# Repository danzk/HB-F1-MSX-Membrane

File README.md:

# MSX Hit Bit Keyboard Membranes

Replacement keyboard membranes for Sony MSX "Hit Bit" home computers.

This repository hosts one design per machine, each in its own directory, all
sharing a common KiCad footprint library.

## Variants

| Machine | Directory | Notes |
| --- | --- | --- |
| Sony HB-F1 | [hb-f1/](hb-f1/) | Original design |
| Sony HB-F1II | [hb-f1ii/](hb-f1ii/) | Reworked PCB with revised switch footprint |

Each variant directory contains its own `pcb/` (KiCad project), `gerber/`
(fabrication outputs) and `mech/` (mechanical drawings), plus a `doc/`
folder for any variant-specific images. Reference material and renders
shared across variants live in the top-level [doc/](doc/) directory.

## Shared footprint library

Both projects reference the same footprints in
[footprints/Sony_Hit_Bit.pretty/](footprints/Sony_Hit_Bit.pretty/) via each
project's `fp-lib-table` (`${KIPRJMOD}/../../footprints/Sony_Hit_Bit.pretty`).

## Manufacturing

See [doc/MANUFACTURING.md](doc/MANUFACTURING.md) for how to order the membrane
from JLCPCB as a 2-layer flexible PCB (stackup, order settings and stiffener
details).

## Other projects

Related keyboard membrane / replacement projects for other Sony MSX models:

- [RBSC/KeyboardMembrane_SonyF1Xx](https://github.com/RBSC/KeyboardMembrane_SonyF1Xx)
  — replacement membrane PCB and gerbers for the Sony HB-F1XV, HB-F1XD and
  HB-F1XDJ.
- [S0urceror/HB-F1XD-keyboard](https://github.com/S0urceror/HB-F1XD-keyboard)
  — KiCad PCB replacement for the Sony HB-F1XD MSX2 keyboard membrane.

## Tooling

2D mechanical drawings were performed with QCAD v3.31.2.7 — https://www.qcad.org/

Electronics were designed with KiCad v8.0.7 — https://www.kicad.org/

The PCB layout uses the font IBM Plex Sans — https://www.ibm.com/plex/

## Licence

Copyright Alexander Knapik 2025.

This source describes Open Hardware and is licensed under the CERN-OHL-W v2 or later.

You may redistribute and modify this documentation and make products
using it under the terms of the CERN-OHL-W v2 (https://cern.ch/cern-ohl).
This documentation is distributed WITHOUT ANY EXPRESS OR IMPLIED
WARRANTY, INCLUDING OF MERCHANTABILITY, SATISFACTORY QUALITY
AND FITNESS FOR A PARTICULAR PURPOSE. Please see the CERN-OHL-W v2
for applicable conditions.

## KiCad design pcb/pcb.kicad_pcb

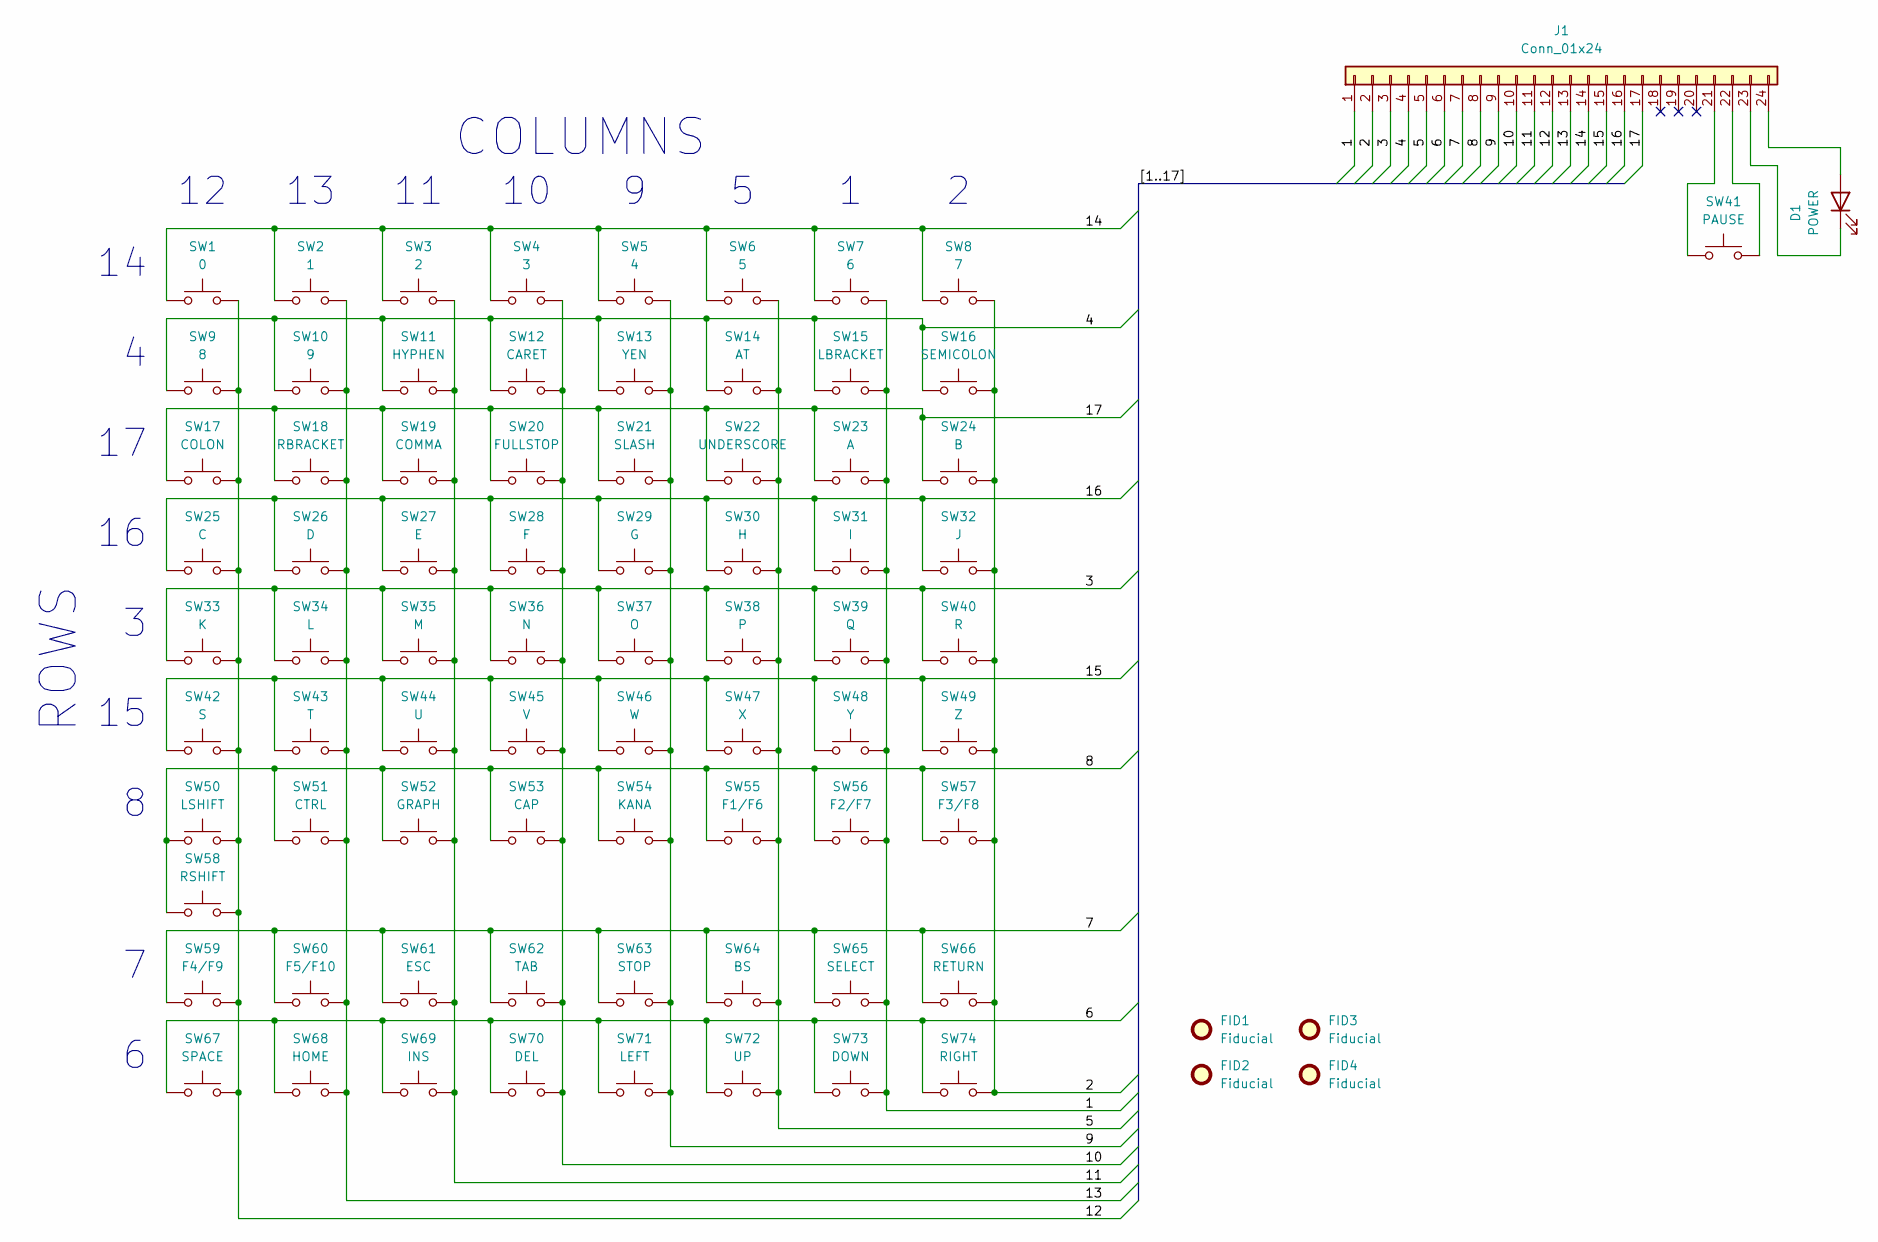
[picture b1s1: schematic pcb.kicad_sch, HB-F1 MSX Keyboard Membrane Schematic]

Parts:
D1: POWER; LED
FID1, FID2, FID3, FID4: Fiducial; Fiducial_1mm_Mask2mm
J1: Conn_01x24; Connector
SW1: 0; Switch
SW2: 1; Switch
SW3: 2; Switch
SW4: 3; Switch
SW5: 4; Switch
SW6: 5; Switch
SW7: 6; Switch
SW8: 7; Switch
SW9: 8; Switch
SW10: 9; Switch
SW11: HYPHEN; Switch
SW12: CARET; Switch
SW13: YEN; Switch
SW14: AT; Switch
SW15: LBRACKET; Switch
SW16: SEMICOLON; Switch
SW17: COLON; Switch
SW18: RBRACKET; Switch
SW19: COMMA; Switch
SW20: FULLSTOP; Switch
SW21: SLASH; Switch
SW22: UNDERSCORE; Switch
SW23: A; Switch
SW24: B; Switch
SW25: C; Switch
SW26: D; Switch
SW27: E; Switch
SW28: F; Switch
SW29: G; Switch
SW30: H; Switch
SW31: I; Switch
SW32: J; Switch
SW33: K; Switch
SW34: L; Switch
SW35: M; Switch
SW36: N; Switch
SW37: O; Switch
SW38: P; Switch
SW39: Q; Switch
SW40: R; Switch
SW41: PAUSE; Switch
SW42: S; Switch
SW43: T; Switch
SW44: U; Switch
SW45: V; Switch
SW46: W; Switch
SW47: X; Switch
SW48: Y; Switch
SW49: Z; Switch
SW50: LSHIFT; Switch
SW51: CTRL; Switch
SW52: GRAPH; Switch
SW53: CAP; Switch
SW54: KANA; Switch
SW55: F1/F6; Switch
SW56: F2/F7; Switch
SW57: F3/F8; Switch
SW58: RSHIFT; Switch
SW59: F4/F9; Switch
SW60: F5/F10; Switch
SW61: ESC; Switch
SW62: TAB; Switch
SW63: STOP; Switch
SW64: BS; Switch
SW65: SELECT; Switch
SW66: RETURN; Switch
SW67: SPACE; Switch
SW68: HOME; Switch
SW69: INS; Switch
SW70: DEL; Switch
SW71: LEFT; Switch
SW72: UP; Switch
SW73: DOWN; Switch
SW74: RIGHT; Switch

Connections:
/1: J1.1, SW7.2, SW15.2, SW23.2, SW31.2, SW39.2, SW48.2, SW56.2, SW65.2, SW73.2
/2: J1.2, SW8.2, SW16.2, SW24.2, SW32.2, SW40.2, SW49.2, SW57.2, SW66.2, SW74.2
/3: J1.3, SW33.1, SW34.1, SW35.1, SW36.1, SW37.1, SW38.1, SW39.1, SW40.1
/4: J1.4, SW9.1, SW10.1, SW11.1, SW12.1, SW13.1, SW14.1, SW15.1, SW16.1
/5: J1.5, SW6.2, SW14.2, SW22.2, SW30.2, SW38.2, SW47.2, SW55.2, SW64.2, SW72.2
/6: J1.6, SW67.1, SW68.1, SW69.1, SW70.1, SW71.1, SW72.1, SW73.1, SW74.1
/7: J1.7, SW59.1, SW60.1, SW61.1, SW62.1, SW63.1, SW64.1, SW65.1, SW66.1
/8: J1.8, SW50.1, SW51.1, SW52.1, SW53.1, SW54.1, SW55.1, SW56.1, SW57.1, SW58.1
/9: J1.9, SW5.2, SW13.2, SW21.2, SW29.2, SW37.2, SW46.2, SW54.2, SW63.2, SW71.2
/10: J1.10, SW4.2, SW12.2, SW20.2, SW28.2, SW36.2, SW45.2, SW53.2, SW62.2, SW70.2
/11: J1.11, SW3.2, SW11.2, SW19.2, SW27.2, SW35.2, SW44.2, SW52.2, SW61.2, SW69.2
/12: J1.12, SW1.2, SW9.2, SW17.2, SW25.2, SW33.2, SW42.2, SW50.2, SW58.2, SW59.2, SW67.2
/13: J1.13, SW2.2, SW10.2, SW18.2, SW26.2, SW34.2, SW43.2, SW51.2, SW60.2, SW68.2
/14: J1.14, SW1.1, SW2.1, SW3.1, SW4.1, SW5.1, SW6.1, SW7.1, SW8.1
/15: J1.15, SW42.1, SW43.1, SW44.1, SW45.1, SW46.1, SW47.1, SW48.1, SW49.1
/16: J1.16, SW25.1, SW26.1, SW27.1, SW28.1, SW29.1, SW30.1, SW31.1, SW32.1
/17: J1.17, SW17.1, SW18.1, SW19.1, SW20.1, SW21.1, SW22.1, SW23.1, SW24.1
unnamed: D1.2 (A), J1.24
unnamed: D1.1 (K), J1.23
unnamed: J1.21, SW41.1
unnamed: J1.22, SW41.2

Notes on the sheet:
COLUMNS
ROWS

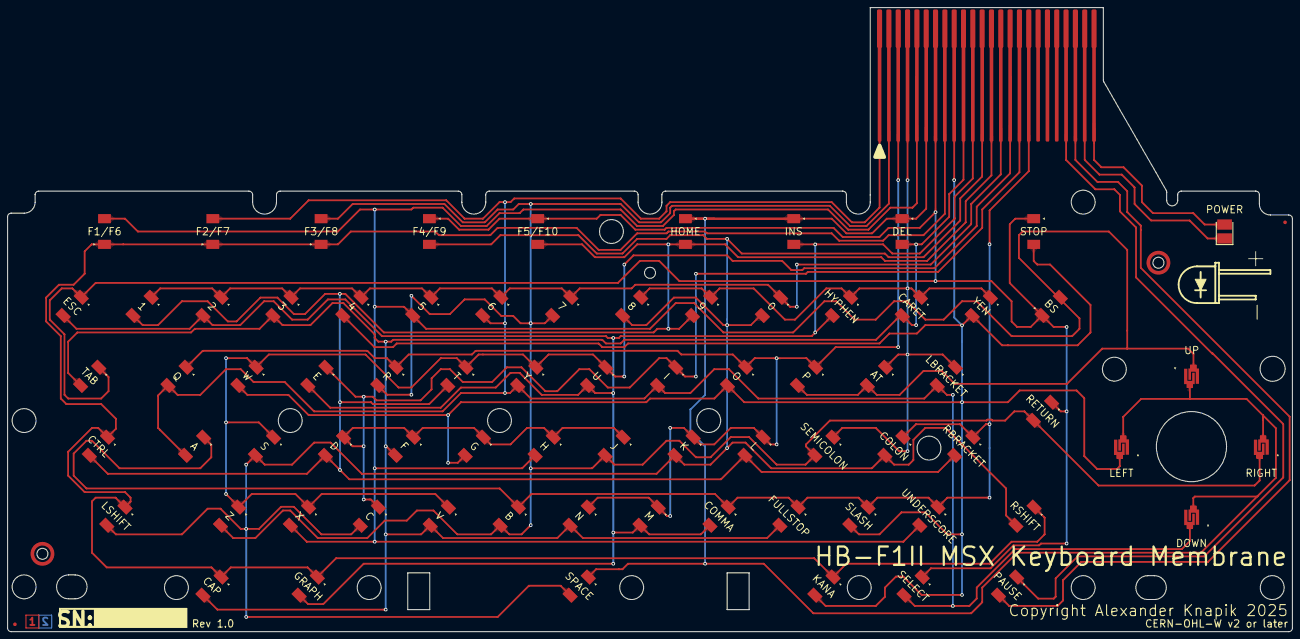
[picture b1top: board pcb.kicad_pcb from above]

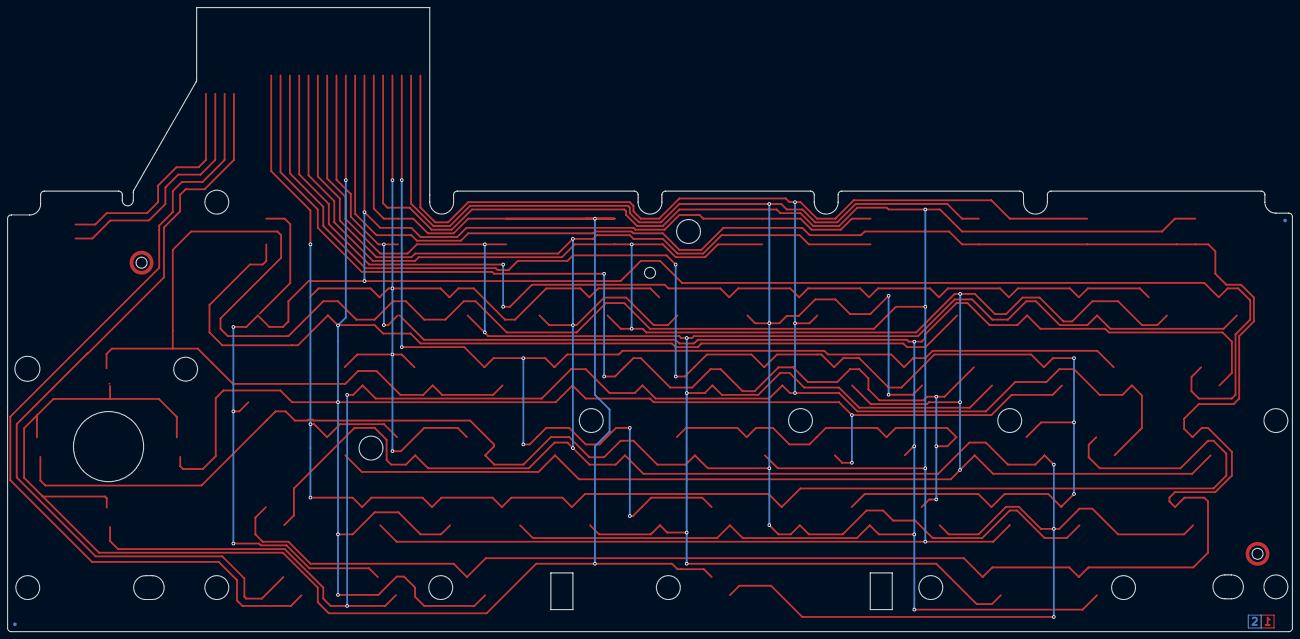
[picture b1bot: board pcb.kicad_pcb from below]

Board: 2 copper layers, 350.0 x 170.0 mm, 80 parts (2 on the bottom side), 21 nets.

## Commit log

2025-01-03 Membrane 2D Drawing
2025-01-03 Completed schematics
2025-01-03 Component placement
2025-01-05 PCB stackup definitions
2025-01-05 Track routing
2025-01-06 Updating footprints and adding PCB labels
2025-01-06 README.md adding PCB render
2025-01-07 PCB fixing position errors and adding labels
2025-01-07 PCB adding fiducials
2025-01-07 README.md updating tools used and licence info
2025-01-07 Generating gerber files
2025-01-07 README.md fixing link typo
2025-01-07 Adding PDF schematic to /doc
2025-01-07 PCB via fiducials and routing optimisations
2025-01-11 Reviewing PCB and updating switch spacing
    Changed soldermask layer on the connector to not be along the whole
    trace. Reviewed the pinout of all the switches and confirmed they're
    good. Reviewed the spacing of the switches and found errors, I have
    moved them but am yet to reroute the traces. Updated the teardrops to be
    curved.
2025-01-11 Rerouted the deleted traces
2025-01-11 Adding stiffener and fab notes
2025-01-11 Adding serial number label
2025-01-11 Reworked PCB and stiffener thickness
2025-01-11 Updating documents for rev 1.0
2025-01-11 Using knockout text for pause key
2025-02-23 Updated README.md
    Updated readme with more images of the actual membrane.
2025-03-02 Updated PCB to Support HBF1II
2025-03-02 Added Render and cleaned up traces
2025-03-02 Added Low Res Membrane Scan
2026-06-08 Restructure HB-F1 into variant subdirectory
    Move the HB-F1 KiCad project, gerbers, docs and mechanical drawings
    under hb-f1/ and hoist the shared Sony_Hit_Bit footprint library to a
    top-level footprints/ directory. Update fp-lib-table to reference the
    shared library and ignore VSCode local history.
    Prepares the repo to host multiple Hit Bit membrane variants side by
    side (HB-F1, HB-F1II).
2026-06-08 Restructure HB-F1II into variant subdirectory
    Move the HB-F1II KiCad project, gerbers, docs and mechanical drawings
    under hb-f1ii/ and hoist the shared Sony_Hit_Bit footprint library
    (including the F1II Switch 2 footprint) to a top-level footprints/
    directory. Update fp-lib-table to reference the shared library.
    Mirrors the hb-f1/ layout so both variants can be merged onto one
    branch without colliding on the shared pcb.kicad_pcb filename.
2026-06-08 Add top-level variant index and per-variant READMEs
    Turn the root README into an index linking the HB-F1 and HB-F1II
    variants and documenting the shared footprint library layout. Add
    focused READMEs inside each variant directory.
2026-06-08 Dedupe shared docs into a top-level doc/ directory
    The HB-F1 and HB-F1II doc folders held 12 byte-identical files
    (keyboard/membrane reference images, pinout and shared PCB renders).
    Consolidate them into a single root doc/ and keep only the three
    HB-F1II-specific images under hb-f1ii/doc/. Update README image links
    accordingly.
2026-06-08 Update to KiCad 10
2026-06-08 add HB-F1II warning
2026-06-08 Add JLCPCB flexible PCB manufacturing guide
    Document how to order the membrane from JLCPCB as a 2-layer flex PCB,
    derived from the Board/Stiffener Characteristics and stackup on the
    User.Comments layer: file set, order settings, the polyimide stiffener
    (User.1 layer) and a pre-order checklist. Link it from the root README.
2026-06-08 Align manufacturing guide wording with JLCPCB quote form
    Use the verbatim field labels and option strings from the JLCPCB FPC
    order form (Base Material 'Flex', Stiffener 'Polyimide', Surface Finish
    'ENIG', Gold Fingers/Castellated Holes 'No', Delivery Format 'Single
    PCB'). Note that the PCB Thickness and Outer Copper Weight option lists
    switch to flex values only after Base Material is set to Flex.
2026-06-08 Add Other projects section to README
    Link related Sony MSX keyboard membrane projects (RBSC F1Xx series and
    S0urceror HB-F1XD).
2026-06-08 Note HB-F1 board has been manufactured at JLCPCB
    The 350x170 mm size is confirmed within JLCPCB's flex limit since the
    HB-F1 board has been fabricated; HB-F1II shares the same outline.
